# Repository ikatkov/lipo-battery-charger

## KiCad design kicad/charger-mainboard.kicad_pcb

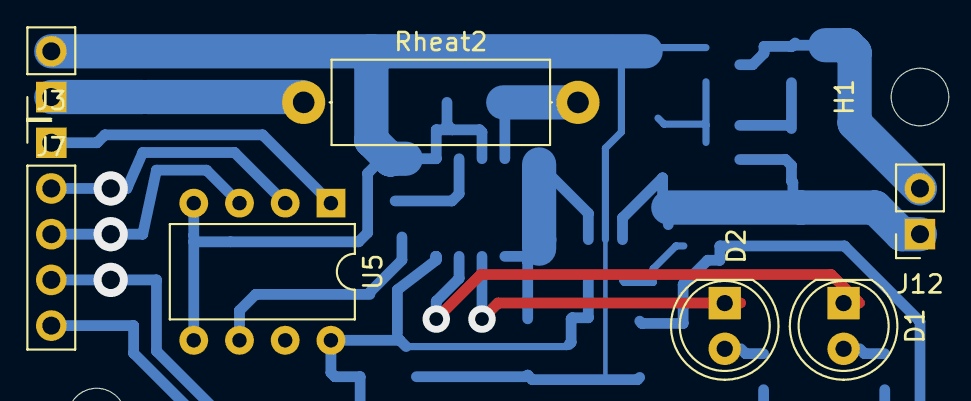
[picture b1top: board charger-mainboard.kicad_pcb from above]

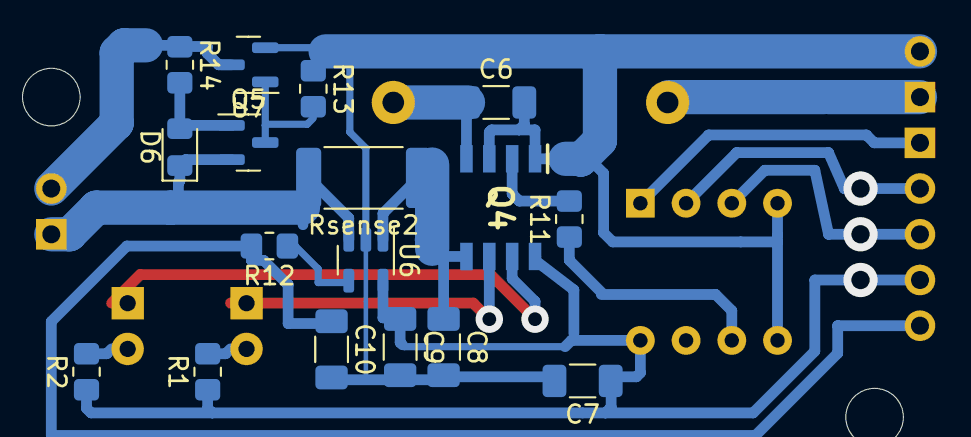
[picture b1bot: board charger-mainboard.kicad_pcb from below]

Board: 4 copper layers, 26 parts (17 on the bottom side), 20 nets.

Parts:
C6, C7, C9: 100nF; C_1206_3216Metric_Pad1.33x1.80mm_HandSolder
C8: 10uF; C_1206_3216Metric_Pad1.33x1.80mm_HandSolder
C10: 470nF; C_1206_3216Metric_Pad1.33x1.80mm_HandSolder
D1: RED_BAT2; LED_D5.0mm
D2: GREEN_BAT2; LED_D5.0mm
D6: BLUE_LED; LED_0805_2012Metric_Pad1.15x1.40mm_HandSolder
H1, H2: MountingHole; MountingHole_3.2mm_M3
J3: Conn_01x05_Female; PinHeader_1x05_P2.54mm_Vertical
J7: Conn_PWR_TROUGH; PinSocket_1x02_P2.54mm_Vertical
J12: Conn_01x02_Female; PinSocket_1x02_P2.54mm_Vertical
Q4: TP4056; SOP-8
Q5: 2N3906; SOT-23
R1, R2, R11: 1k; R_0805_2012Metric_Pad1.20x1.40mm_HandSolder
R12, R13, R14: 10k; R_0805_2012Metric_Pad1.20x1.40mm_HandSolder
Rheat2: 0.4; R_Axial_DIN0414_L11.9mm_D4.5mm_P15.24mm_Horizontal
Rsense2: 0.150; R_2512_6332Metric_Pad1.40x3.35mm_HandSolder
U5: MCP4131 10k; DIP-8_W7.62mm
U6: INA180B1; SOT-23-5
U7: AO3406; SOT-23

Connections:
5V: J7.1, Rheat2.1
+3V3: C7.1, C9.1, J3.4, Q4.8 (CE), R1.1, R2.1, U5.8 (VDD), U6.5 (V+)
BAT2_CHRG: D1.1 (K), Q4.7 (~CHRG)
BAT2_NEG: J12.2, R14.1, U7.3 (D)
BAT2_POS: D6.1 (K), J12.1, Q5.2 (E), Rsense2.2, U6.3 (-)
BAT2_STDBY: D2.1 (K), Q4.6 (~STDBY)
CH2_CS: J3.1, U5.1 (~CS)
CH2_Isense: C10.1, J3.5, R12.2
CH2_PROG: Q4.2 (PROG), R11.2
GND: C6.2, C7.2, C8.2, C9.2, C10.2, J7.2, Q4.1 (TEMP), Q4.3 (GND), R13.1, U5.4 (VSS), U5.5 (PA0), U6.2 (GND), U7.2 (S)
MOSI: J3.3, U5.3 (SI)
unnamed: C6.1, Q4.4 (VCC), Rheat2.2
unnamed: C8.1, Q4.5 (BAT), Rsense2.1, U6.1 (+)
unnamed: D1.2 (A), R2.2
unnamed: D2.2 (A), R1.2
unnamed: D6.2 (A), Q5.1 (B), R14.2
unnamed: Q5.3 (C), R13.2, U7.1 (G)
unnamed: R11.1, U5.6 (PW0)
unnamed: R12.1, U6.4
SCK: J3.2, U5.2 (SCK)

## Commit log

2022-09-07 with MCP4551
2022-09-07 folder rename
2022-09-08 before-deleting-1st-channel
2022-12-07 all-the-changes
2022-12-07 added text narratice around IIR
2022-12-07 typo
2022-12-07 added zeros and poles unit circle plot
